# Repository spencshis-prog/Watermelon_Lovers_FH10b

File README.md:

# Watermelon Lovers 🍉

**Watermelon Lovers** is a senior design project developed at the **University of Texas at Austin**. The project aims to create a consumer-friendly tool that evaluates the quality and ripeness of watermelons using acoustic and visual analysis techniques. By leveraging machine learning and signal processing, this tool will help users make informed decisions while shopping for watermelons at grocery stores and markets.

This repository contains the codebase for the project, including a frontend for user interaction and a backend (currently under development) for data processing and evaluation.

---

## Project Structure

- **frontend/**: Contains the user-facing application, built using Python's Flask framework.
  - `app.py`: The main entry point for the frontend server.
  - `templates/`: HTML templates for the application's web pages.
    - `home`: The landing page where users can upload their data.
    - `results`: Displays the evaluation of watermelon quality and ripeness.
  - `uploads/`: Stores user-uploaded files (e.g., images or acoustic data).

- **backend/**: Reserved for future development, including the core machine learning and data processing logic.

- - **watermelon_acoustic scripts/**:
  - `main.py`: Orchestrates the entire pipeline. Configures paths, calls each stage (preprocessing, standardization, noise reduction, model training, testing), and ensures a smooth flow from raw data to final evaluation.
  - `wav_file_converter.py`: Converts `.m4a` files to `.wav` (and handles other basic format conversions) so all audio data is in a consistent `.wav` format.
  - `standardize_wav.py`: Ensures each `.wav` file meets uniform specs (sample rate, mono channel, 16-bit PCM, exact duration, etc.). Trims or pads audio as needed.
  - `noise_reduction.py`: Applies one or more noise reduction or filtering techniques (e.g. low-pass filter, gain adjustments) to improve audio clarity before model training.
  - `model_training.py`: Loads the standardized/noise-reduced `.wav` files, parses labels from filenames, splits data into train/val/test, and trains a machine learning model (e.g., an LSTM) to predict watermelon sweetness (Brix).
  - `model_testing.py`: Loads trained models and tests them against a specified dataset (e.g., a hold-out test set), computing metrics like MAE, MSE, and R². Can also generate visual charts (bar charts, scatter plots, etc.) comparing model performance.

---

## Getting Started

### Prerequisites

- **Python 3.9 or later**
- Required Python packages (install via pip):
  ```bash
  pip install flask

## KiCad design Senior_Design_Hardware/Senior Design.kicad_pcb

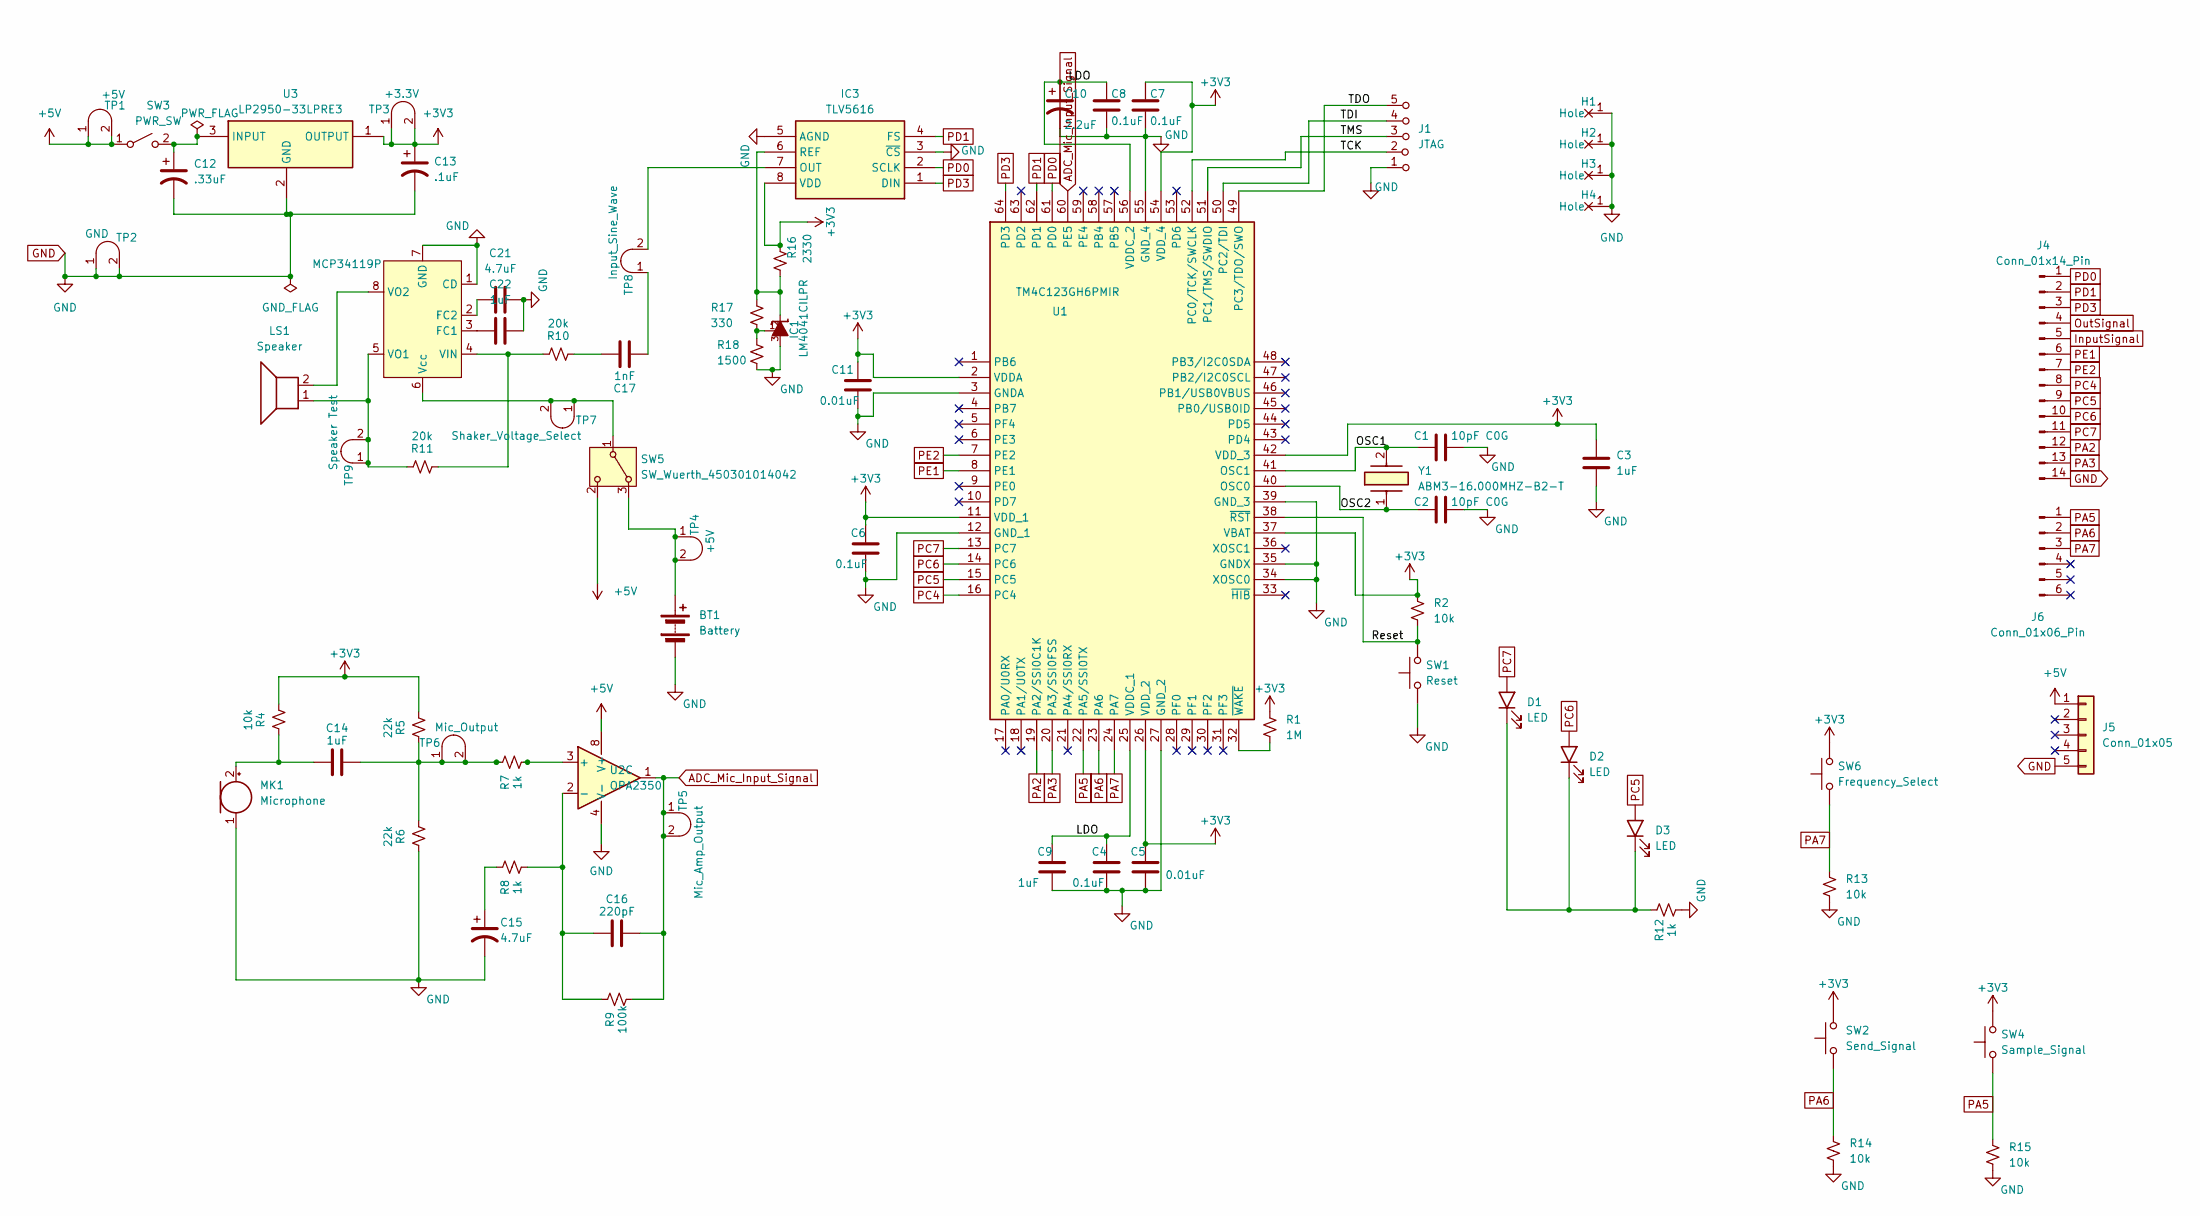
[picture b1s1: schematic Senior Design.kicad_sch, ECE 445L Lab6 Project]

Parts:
BT1: Battery
C1, C2: 10pF C0G; C_Axial_200mil
C3, C9, C14, C22: 1uF; C_Axial_200mil
C4, C6, C7, C8: 0.1uF; C_Axial_200mil
C5, C11: 0.01uF; C_Axial_200mil
C10: 2.2uF; CP_Radial_Tantal200mil
C12: .33uF; CP_Radial_Tantal200mil
C13: .1uF; CP_Radial_Tantal200mil
C15: 4.7uF; CP_Radial_Tantal200mil
C16: 220pF; C_Axial_200mil
C17: 1nF; C_Axial_200mil
C21: 4.7uF; C_Axial_200mil
D1, D2, D3: LED; LED_D5.0mm
H1, H2, H3, H4: MountingHole_4_40
IC1: LM4041CILPR; ti_LM4041CILPR
IC3: TLV5616; DIP-8_W7.62mm_LongPads
J1: JTAG; PinHeader_1x05_P2.54mm_Vertical
J4: Conn_01x14_Pin; PinHeader_1x14_P1.00mm_Vertical_SMD_Pin1Left
J5: Conn_01x05; PinHeader_1x05_P1.00mm_Vertical
J6: Conn_01x06_Pin; PinHeader_1x06_P1.00mm_Vertical_SMD_Pin1Left
LS1: Speaker
MK1: Microphone
R1: 1M; R_Axial_DIN0204_L3.6mm_D1.6mm_P7.62mm_Horizontal
R2, R4, R13, R14, R15: 10k; R_Axial_DIN0204_L3.6mm_D1.6mm_P7.62mm_Horizontal
R5, R6: 22k; R_Axial_DIN0204_L3.6mm_D1.6mm_P7.62mm_Horizontal
R7, R8, R12: 1k; R_Axial_DIN0204_L3.6mm_D1.6mm_P7.62mm_Horizontal
R9: 100k; R_Axial_DIN0204_L3.6mm_D1.6mm_P7.62mm_Horizontal
R10, R11: 20k; R_Axial_DIN0204_L3.6mm_D1.6mm_P7.62mm_Horizontal
R16: 2330; R_Axial_DIN0204_L3.6mm_D1.6mm_P7.62mm_Horizontal
R17: 330; R_Axial_DIN0204_L3.6mm_D1.6mm_P7.62mm_Horizontal
R18: 1500; R_Axial_DIN0204_L3.6mm_D1.6mm_P7.62mm_Horizontal
SW1: Reset; SW_PUSH_6mm
SW2: Send_Signal; SW_PUSH_6mm
SW3: PWR_SW; SW_SPST_B3S-1000
SW4: Sample_Signal; SW_PUSH_6mm
SW5: SW_Wuerth_450301014042; SW_Slide-03_Wuerth-WS-SLTV_10x2.5x6.4_P2.54mm
SW6: Frequency_Select; SW_PUSH_6mm
TP1, TP4: +5V; Testpoint_1x02_P2.54mm
TP2: GND; Testpoint_1x02_P2.54mm
TP3: +3.3V; Testpoint_1x02_P2.54mm
TP5: Mic_Amp_Output; Testpoint_1x02_P2.54mm
TP6: Mic_Output; Testpoint_1x02_P2.54mm
TP7: Shaker_Voltage_Select; Testpoint_1x02_P2.54mm
TP8: Input_Sine_Wave; Testpoint_1x02_P2.54mm
TP9: Speaker Test; Testpoint_1x02_P2.54mm
U1: TM4C123GH6PMIR; QFP50P1200X1200X160-64N; Mouser Part Number 595-TM4C123GH6PMIR
U2: OPA2350; DIP-8_W7.62mm_LongPads
U3: LP2950-33LPRE3; TL431CLPM; Mouser Part Number 595-LP2950-33LPRE3
U6: MCP34119P; DIP-8_W7.62mm_LongPads
Y1: ABM3-16.000MHZ-B2-T; ABM3; Mouser Part Number 815-ABM3-16-B2-T

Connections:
+3V3: C3.1, C5.1, C6.1, C7.1, C11.1, C13.1, IC3.8 (VDD), R1.1, R2.1, R4.1, R5.1, R16.1, SW2.2, SW4.2, SW6.2, TP3.1 (A), TP3.2 (B), U1.2 (VDDA), U1.11 (VDD_1), U1.26 (VDD_2), U1.37 (VBAT), U1.42 (VDD_3), U1.54 (VDD_4), U3.1 (OUTPUT)
+5V: J5.1, SW3.1 (A), SW5.2 (C), TP1.1 (A), TP1.2 (B), U2.8 (V+)
/LDO: C4.1, C8.1, C9.1, C10.1, U1.25 (VDDC_1), U1.56 (VDDC_2)
/OSC1: C1.1, U1.41 (OSC1), Y1.2
/OSC2: C2.1, U1.40 (OSC0), Y1.1
/Reset: R2.2, SW1.2, U1.38 (~RST)
/TCK: J1.2 (B), U1.52 (PC0/TCK/SWCLK)
/TDI: J1.4 (C), U1.50 (PC2/TDI)
/TDO: J1.5 (C), U1.49 (PC3/TDO/SWO)
/TMS: J1.3 (C), U1.51 (PC1/TMS/SWDIO)
ADC_Mic_Input_Signal: C16.2, R9.1, TP5.1 (A), TP5.2 (B), U1.60 (PE5), U2.1
GND: BT1.2 (-), C1.2, C2.2, C3.2, C4.2, C5.2, C6.2, C7.2, C8.2, C9.2, C10.2, C11.2, C12.2, C13.2, C15.2, C21.2, C22.2, H1.1, H2.1, H3.1, H4.1, IC1.3, IC3.3 (~CS), IC3.5 (AGND), J1.1 (A), J4.14, J5.5, MK1.1 (-), R6.2, R12.1, R13.2, R14.2, R15.2, R18.2, SW1.1, TP2.1 (A), TP2.2 (B), U1.3 (GNDA), U1.12 (GND_1), U1.27 (GND_2), U1.34 (XOSC0), U1.35 (GNDX), U1.39 (GND_3), U1.55 (GND_4), U2.4 (V-), U3.2 (GND), U6.1 (CD), U6.7 (GND)
InputSignal: J4.5
unnamed: BT1.1 (+), SW5.3 (A), TP4.1 (A), TP4.2 (B)
unnamed: C15.1, R8.2
unnamed: C17.2, R10.1
unnamed: D1.1 (K), D2.1 (K), D3.1 (K), R12.2
unnamed: IC1.1, R17.2, R18.1
unnamed: IC3.7 (OUT), TP8.2 (B)
unnamed: IC1.2, IC3.6 (REF), R16.2, R17.1
unnamed: C14.1, MK1.2 (+), R4.2
unnamed: C12.1, SW3.2 (B), U3.3 (INPUT)
unnamed: SW5.1 (B), TP7.1 (A), TP7.2 (B), U6.6 (Vcc)
unnamed: C14.2, R5.2, R6.1, R7.2, TP6.1 (A), TP6.2 (B)
unnamed: C17.1, TP8.1 (A)
unnamed: LS1.1, R11.2, TP9.1 (A), TP9.2 (B), U6.5 (VO1)
unnamed: R1.2, U1.32 (~WAKE)
unnamed: R7.1, U2.3 (+)
unnamed: C16.1, R8.1, R9.2, U2.2 (-)
unnamed: C22.1, U6.3 (FC1)
unnamed: C21.1, U6.2 (FC2)
unnamed: R10.2, R11.1, U6.4 (VIN)
unnamed: LS1.2, U6.8 (VO2)
OutSignal: J4.4
PA2: J4.12, U1.19 (PA2/SSI0C1K)
PA3: J4.13, U1.20 (PA3/SSI0FSS)
PA5: J6.1, R15.1, SW4.1, U1.22 (PA5/SSI0TX)
PA6: J6.2, R14.1, SW2.1, U1.23 (PA6)
PA7: J6.3, R13.1, SW6.1, U1.24 (PA7)
PC4: J4.8, U1.16 (PC4)
PC5: D3.2 (A), J4.9, U1.15 (PC5)
PC6: D2.2 (A), J4.10, U1.14 (PC6)
PC7: D1.2 (A), J4.11, U1.13 (PC7)
PD0: IC3.2 (SCLK), J4.1, U1.61 (PD0)
PD1: IC3.4 (FS), J4.2, U1.62 (PD1)
PD3: IC3.1 (DIN), J4.3, U1.64 (PD3)
PE1: J4.6, U1.8 (PE1)
PE2: J4.7, U1.7 (PE2)

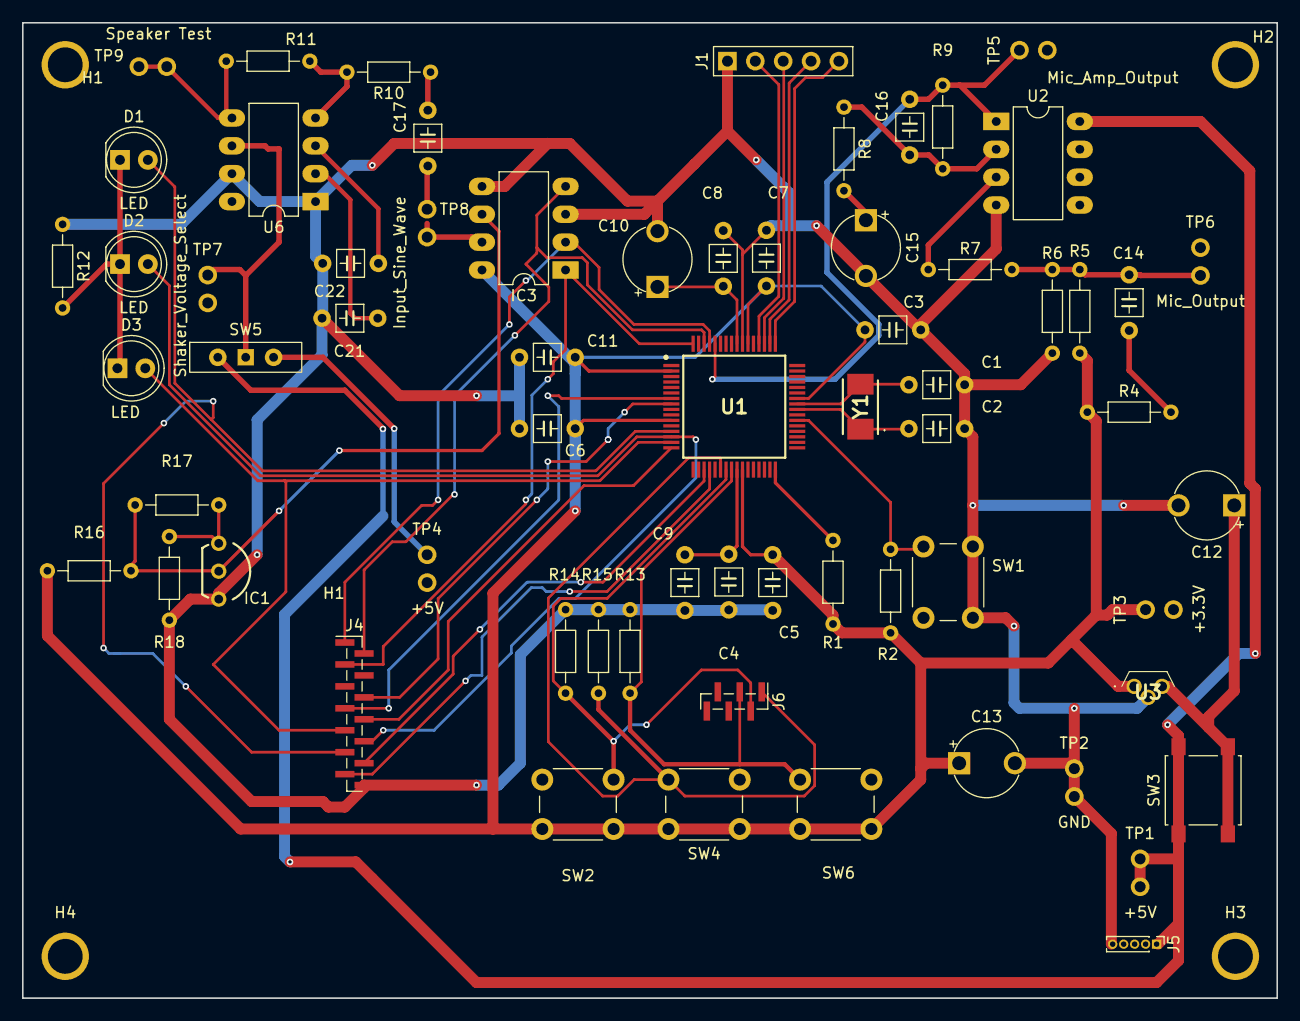
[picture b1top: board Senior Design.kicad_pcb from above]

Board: 2 copper layers, 114.4 x 88.9 mm, 69 parts (0 on the bottom side), 45 nets.

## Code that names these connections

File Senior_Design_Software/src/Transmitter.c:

// File **********Transmitter.c***********
// Lab 5
// Programs to implement transmitter functionality   
// EE445L Spring 2021
//    Jonathan W. Valvano 4/4/21
// Hardware/software assigned to transmitter
//   UART0, possible source of input data (conflicts with TExaSdisplay)
//   PC7-PC4 Port_C_Init, possible source of input data
//   Timer0A periodic interrupt to generate input
//   FreqFifo linkage from Encoder to SendData
//   Timer1A periodic interrupt create a sequence of frequencies
//   SSI1 PD3 PD1 PD0 TLV5616 DAC output
//   SysTick ISR output to DAC

#include <stdint.h>
#include "../inc/tm4c123gh6pm.h"
#include "../inc/Timer0A.h"
#include "../inc/Timer1A.h"
#include "../inc/fifo.h"
#include "../inc/tlv5616.h"
    // write this
   
#include <stdint.h>
#include "../inc/tm4c123gh6pm.h"
#include "../inc/CortexM.h"
#include "../inc/SysTickInts.h"
//#include "UART.h"
#define WAVE_TABLE_SIZE 256       


#define CR   0x0D
#define LF   0x0A


// **************SysTick_Init*********************
// Initialize SysTick periodic interrupts
// Input: interrupt period
//        Units of period are 12.5ns (assuming 80 MHz clock)
//        Maximum is 2^24-1
//        Minimum is determined by length of ISR
// Output: none





int signalOne = 0;
int signalTwo = 0;
int freq_entered = 0;

static uint32_t WaveIndex = 0;     // Current index in the sine wave table
//static uint32_t Period = 0;        // SysTick period for note frequency


void DelayTransmission(int ms);
void SysTick_SetPeriod(uint32_t);

static const uint16_t SineWave[WAVE_TABLE_SIZE] = {
127, 130, 133, 136, 139, 143, 146, 149, 152, 155, 158, 161, 164, 167, 170, 173,
176, 179, 182, 184, 187, 190, 193, 195, 198, 200,                                                                              203, 205, 208, 210, 213, 215,
217, 219, 221, 224, 226, 228, 229, 231, 233, 235, 236, 238, 239, 241, 242, 244,
245, 246, 247, 248, 249, 250, 251, 251, 252, 253, 253, 254, 254, 254, 254, 254,
255, 254, 254, 254, 254, 254, 253, 253, 252, 251, 251, 250, 249, 248, 247, 246,
245, 244, 242, 241, 239, 238, 236, 235, 233, 231, 229, 228, 226, 224, 221, 219,
217, 215, 213, 210, 208, 205, 203, 200, 198, 195, 193, 190, 187, 184, 182, 179,
176, 173, 170, 167, 164, 161, 158, 155, 152, 149, 146, 143, 139, 136, 133, 130,
127, 124, 121, 118, 115, 111, 108, 105, 102, 99, 96, 93, 90, 87, 84, 81,
78, 75, 72, 70, 67, 64, 61, 59, 56, 54, 51, 49, 46, 44, 41, 39,
37, 35, 33, 30, 28, 26, 25, 23, 21, 19, 18, 16, 15, 13, 12, 10,
9, 8, 7, 6, 5, 4, 3, 3, 2, 1, 1, 0, 0, 0, 0, 0,
0, 0, 0, 0, 0, 0, 1, 1, 2, 3, 3, 4, 5, 6, 7, 8,
9, 10, 12, 13, 15, 16, 18, 19, 21, 23, 25, 26, 28, 30, 33, 35,
37, 39, 41, 44, 46, 49, 51, 54, 56, 59, 61, 64, 67, 70, 72, 75,
78, 81, 84, 87, 90, 93, 96, 99, 102, 105, 108, 111, 115, 118, 121, 124,};




void SysTick_Init(uint32_t period){
	long sr;
  sr = StartCritical();
  NVIC_ST_CTRL_R = 0;         // disable SysTick during setup
  NVIC_ST_RELOAD_R = period-1;// reload value
  NVIC_ST_CURRENT_R = 0;      // any write to current clears it
  NVIC_SYS_PRI3_R = (NVIC_SYS_PRI3_R&0x00FFFFFF)|0x40000000; // priority 2
                              // enable SysTick with core clock and interrupts
  NVIC_ST_CTRL_R = 0x07;
  EndCritical(sr);
}



void selectSignalOne(void){
	signalOne =  1;
	signalTwo = 0;
	
}


void selectSignalTwo(void){
	signalOne =  0;
	signalTwo = 1;
	
}

void noSignal(void){
	signalOne =  0;
	signalTwo = 0;
	
}




void SysTick_SetPeriod(uint32_t newPeriod) {
    NVIC_ST_CTRL_R = 0;
    NVIC_ST_RELOAD_R = newPeriod - 1;
    NVIC_ST_CURRENT_R = 0;
    NVIC_ST_CTRL_R = 0x07; 
}




void SysTick_Handler(void){
	
		if(((GPIO_PORTA_DATA_R & 0x80) == 0x80)){
			DelayTransmission(5000);
			UART_OutString("Enter input frequency (Hz):\r\n");
			freq_entered = UART_InUDec();  
			freq_entered = 80000000 / (freq_entered * 256);
			SysTick_SetPeriod(freq_entered);
			UART_OutChar(CR); UART_OutChar(LF);
			UART_OutString("Input Recived.");
			UART_OutChar(CR); UART_OutChar(LF);
		}
	
		if(((GPIO_PORTF_DATA_R & 0x10) == 0x0)){
			selectSignalOne();
		}else{
			noSignal();
		}

		
		if(signalOne == 1){
			DAC_Out(SineWave[WaveIndex]);
			WaveIndex = (WaveIndex + 1) &0xFF;
		}
}


void DelayTransmission(int ms){
	while(ms > 0) {
        ms--;
    }
}

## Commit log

2024-12-02 fixed README
2025-02-25 wav file converter
    translates raw ADC data to acceptable .wav format for model
2025-03-04 moving
2025-03-06 Initial commit of train_acoustic project
2025-03-06 Update README.md for watermelon_acoustic
2025-03-06 fft and microcontroller code
2025-03-07 microcontroller and port read python file
2025-03-08 fixed model_testing for comparison of various noise reduction techniques
2025-03-08 implemented feature extraction dimension
2025-03-09 preliminary lr_pipeline complete
2025-03-09 completed lr pipeline, reg='none' does not mirror old residual plotting, indicating potential error
2025-03-10 fully completed lr pipeline
2025-03-10 debugged report_kfold, qol changes for preprocessing pipeline, code legibility
2025-03-10 implemented random forest pipeline and comparator dashboard
2025-03-11 unregularized xgboost pipeline complete
2025-03-11 expanded hypertuning, implemented extratrees and catboost pipelines, omitted poorly performing preprocessing combinations, included chroma feature extraction
2025-03-12 added report_params.txt for ease of exploring hyperparameter ranges
2025-03-13 ran on 56 preprocess combinations, added optuna and lightgbm pipelines, weird bug where command line prompts run older version?
2025-03-13 reassessed preprocessing combo elements
2025-03-13 saving for .73 and .72 lgbm models, also starting generic ModelPipeline object
2025-03-15 generalized ModelPipeline object, partially implemented data priming functions
2025-03-20 run w normalization and feature transformations, 4 models w 0.6 r2's compared to 1 model w out normalization and ft's
2025-03-20 2nd degree PolynomialFeatures, SelectKBest where f_regressor with k=50, yielded better results in feature generation and selection
2025-03-26 updates people
2025-03-26 oops
2025-03-26 oops again
2025-03-27 added normalization, feature generation and selection, catboost runs slowly, three models achieved .7X testing r2 error
2025-03-31 collect data from port
2025-03-31 fixed to work with revisions
2025-04-01 quick revisions
2025-04-01 should be gud
2025-04-02 4 0.7 r2 models, implemented mlp & krs, debugged early_stopping_rounds
2025-04-02 debugged xgb partially, many working models, attempting to modularize early stopping better after this commit
2025-04-02 started data collection
2025-04-02 watermelon pictures
2025-04-07 implemented predict.py, gradient boosters rerun for early stopping criteria
2025-04-07 Create vis_model_train.py
    Create vis_model.keras
2025-04-07 path to input
2025-04-07 added vis data fro qilin
2025-04-09 trying to get app better
2025-04-15 sample vis_deployment
2025-04-23 Create UART8bit
2025-04-25 commit prior to lab conditions
2025-04-26 dataset_size=15, ran on recording technique b, use 15_{model and predict}_ssd_chroma_xgb_default.{pkl and py}
2025-04-26 fixed minor bug with chroma extraction tehcnique in the predict.py
2025-04-26 added selector and transformer
2025-04-26 best 5 models + requirements from rf, et, lgbm...subsequent trainings on pruned xgb and cat
2025-04-26 xgb under standard params scored .66, further param tuning subsequently
2025-04-26 USE 74_steg_mfcc_xgb_random directory, look at read-me for performance/implications
